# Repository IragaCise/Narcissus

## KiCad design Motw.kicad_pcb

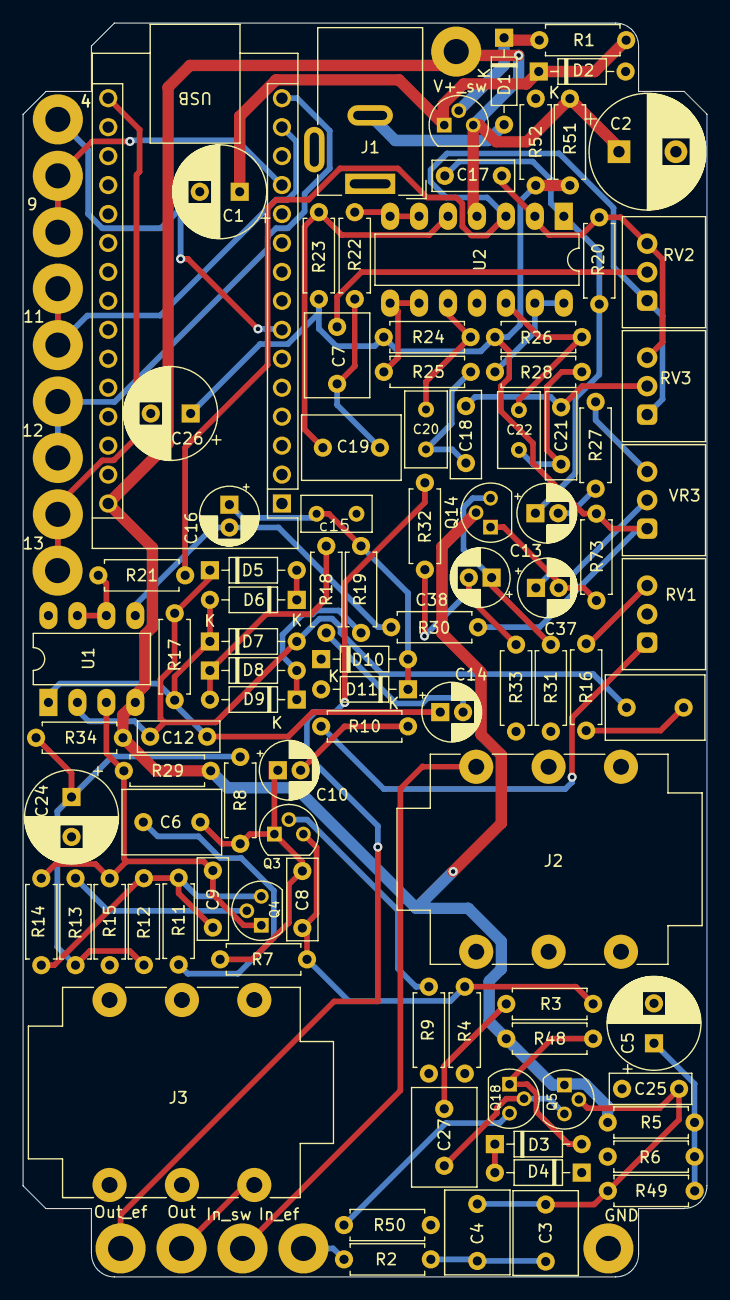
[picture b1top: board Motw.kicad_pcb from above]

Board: 2 copper layers, 60.0 x 110.0 mm, 110 parts (0 on the bottom side), 62 nets.

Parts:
4, 9, 9#2, 11, 11#2, 12, 12#2, 13, 13#2: MountingHole_Pad; MountingHole_2.2mm_M2_Pad
A1: Arduino_Nano_v3.x; Arduino_Nano
C1, C5, C26: 47u; CP_Radial_D8.0mm_P3.50mm
C2: 100u; CP_Radial_D10.0mm_P5.00mm
C3, C4: 1u; C_Rect_L7.2mm_W5.5mm_P5.00mm_FKS2_FKP2_MKS2_MKP2
C6: 47n; C_Rect_L8.5mm_W5.5mm_P5.00mm_FKS2_FKP2_MKS2_MKP2
C7: 47u; C_Rect_L7.2mm_W5.5mm_P5.00mm_FKS2_FKP2_MKS2_MKP2
C8: 100p; C_Rect_L7.0mm_W2.5mm_P5.00mm
C9: 10u; C_Rect_L7.0mm_W2.5mm_P5.00mm
C10: 47n; CP_Radial_D5.0mm_P2.00mm
C11: 100p; C_Rect_L8.5mm_W5.5mm_P5.00mm_FKS2_FKP2_MKS2_MKP2
C12: 47n; C_Rect_L7.0mm_W2.5mm_P5.00mm
C13: 100p; CP_Radial_D5.0mm_P2.00mm
C14: 1u; CP_Radial_D5.0mm_P2.00mm
C15: 68n; C_Rect_L6.0mm_W3.0mm_P3.50mm_MKS02_FKP02
C16: 4.7n; CP_Radial_D5.0mm_P2.00mm
C17: 6.8n; C_Rect_L7.0mm_W2.5mm_P5.00mm
C18: 1n; C_Rect_L7.5mm_W3.0mm_P5.00mm
C19: 1u; C_Rect_L8.5mm_W5.5mm_P5.00mm_FKS2_FKP2_MKS2_MKP2
C20: 1.5u; C_Rect_L6.5mm_W3.5mm_P3.50mm_MKS02_FKP02
C21: 0.1u; C_Rect_L7.5mm_W3.0mm_P5.00mm
C22: 0.15u; C_Rect_L6.5mm_W3.5mm_P3.50mm_MKS02_FKP02
C24: 10u; CP_Radial_D8.0mm_P3.50mm
C25: 150p; C_Rect_L7.0mm_W2.5mm_P5.00mm
C27: 10u; C_Rect_L8.5mm_W5.5mm_P5.00mm_FKS2_FKP2_MKS2_MKP2
C37, C38: 10u; CP_Radial_D5.0mm_P2.00mm
D1: 1N4007; D_DO-35_SOD27_P7.62mm_Horizontal
D2: VF=11V; D_DO-35_SOD27_P7.62mm_Horizontal
D3, D4, D5, D6, D7, D10, D11: 1N4148; D_DO-35_SOD27_P7.62mm_Horizontal
D8, D9: 1N34A; D_DO-35_SOD27_P7.62mm_Horizontal
GND: MountingHole_Pad; MountingHole_2.2mm_M2_Pad
In_ef: MountingHole_Pad; MountingHole_2.2mm_M2_Pad
In_sw: MountingHole_Pad; MountingHole_2.2mm_M2_Pad
J1: Barrel_Jack_Switch; BarrelJack_Effector
J2: AudioJack3; Jack_6.35mm_Neutrik_NMJ6HCD2_Horizontal
J3: AudioJack2; Jack_6.35mm_Neutrik_NMJ6HCD2_Horizontal
Out: MountingHole_Pad; MountingHole_2.2mm_M2_Pad
Out_ef: MountingHole_Pad; MountingHole_2.2mm_M2_Pad
Q1, Q4, Q14, Q18: 2SC2240; TO-92_231
Q3: 2SA970; TO-92_231
Q5: 2SK30A; TO-92
R1: 2.2k; R_Axial_DIN0207_L6.3mm_D2.5mm_P7.62mm_Horizontal
R2, R9, R16, R20, R24, R33: 10k; R_Axial_DIN0207_L6.3mm_D2.5mm_P7.62mm_Horizontal
R3: 1k; R_Axial_DIN0207_L6.3mm_D2.5mm_P7.62mm_Horizontal
R4, R12: 22k; R_Axial_DIN0207_L6.3mm_D2.5mm_P7.62mm_Horizontal
R5, R6, R48, R51, R52: 33k; R_Axial_DIN0207_L6.3mm_D2.5mm_P7.62mm_Horizontal
R7, R13, R21, R22, R32, R34, R73: 100k; R_Axial_DIN0207_L6.3mm_D2.5mm_P7.62mm_Horizontal
R8, R14: 470k; R_Axial_DIN0207_L6.3mm_D2.5mm_P7.62mm_Horizontal
R10: 22; R_Axial_DIN0207_L6.3mm_D2.5mm_P7.62mm_Horizontal
R11: 150; R_Axial_DIN0207_L6.3mm_D2.5mm_P7.62mm_Horizontal
R15: 120; R_Axial_DIN0207_L6.3mm_D2.5mm_P7.62mm_Horizontal
R17, R28: 68k; R_Axial_DIN0207_L6.3mm_D2.5mm_P7.62mm_Horizontal
R18: 47k; R_Axial_DIN0207_L6.3mm_D2.5mm_P7.62mm_Horizontal
R19: 220k; R_Axial_DIN0207_L6.3mm_D2.5mm_P7.62mm_Horizontal
R23: 82k; R_Axial_DIN0207_L6.3mm_D2.5mm_P7.62mm_Horizontal
R25, R26, R27: 330; R_Axial_DIN0207_L6.3mm_D2.5mm_P7.62mm_Horizontal
R29, R30: 3.3k; R_Axial_DIN0207_L6.3mm_D2.5mm_P7.62mm_Horizontal
R31: 4.7k; R_Axial_DIN0207_L6.3mm_D2.5mm_P7.62mm_Horizontal
R49: 1M; R_Axial_DIN0207_L6.3mm_D2.5mm_P7.62mm_Horizontal
R50: 470; R_Axial_DIN0207_L6.3mm_D2.5mm_P7.62mm_Horizontal
RV1: 250k; Potentiometer_RD9
RV2, RV3: 10k; Potentiometer_RD9
U1: TL072; DIP-8_W7.62mm_LongPads
U2: TL074; DIP-14_W7.62mm_LongPads
V+_sw: MountingHole_Pad; MountingHole_2.2mm_M2_Pad
VR3: 10k; Potentiometer_RD9

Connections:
+4V: C26.1, R21.1, R22.1, R23.1, R28.2, R32.2, R51.2, R52.1, R73.2, VR3.1
+8V: A1.30 (VIN), C2.1, Q1.2 (E), Q4.3 (C), Q5.1 (D), Q14.3 (C), R3.1, R5.1, R17.2, R48.2, R51.1, U1.4 (V-), U2.4 (V+), V+_sw.1
+9V: D1.1 (K), Q1.3 (C), R1.1
GND: A1.4 (GND), A1.29 (GND), C1.2, C2.2, C5.2, C7.2, C18.2, C25.2, C26.2, D2.2 (A), D4.1 (K), D10.1 (K), D11.2 (A), GND.1, J1.1, J2.S, J3.S, R6.2, R7.1, R10.1, R16.1, R33.2, R34.2, R50.2, R52.2, RV1.2, U1.8 (V+), U2.11 (V-)
unnamed: 4.1, A1.7 (D4)
unnamed: 9.1, 9#2.1, A1.12 (D9)
unnamed: 11.1, 11#2.1, A1.14 (D11)
unnamed: 12.1, 12#2.1, A1.15 (D12)
unnamed: 13.1, 13#2.1, A1.16 (D13)
unnamed: C3.2, C4.2, R2.2
unnamed: C5.1, R5.2, R6.1, R49.2
unnamed: C6.2, R4.1
unnamed: C7.1, R3.2, R9.2, R13.2, R15.2
unnamed: C9.2, R11.2
unnamed: C10.2, R12.1
unnamed: C12.2, R18.2
unnamed: C14.2, R20.1
unnamed: C15.2, C20.1, R25.2
unnamed: C16.2, C21.1, R26.2
unnamed: C17.2, C22.1, R27.2
unnamed: C20.2, RV2.2
unnamed: C21.2, C22.2, RV3.2
unnamed: C24.1, R30.2, U2.1
unnamed: C24.2, R31.2
unnamed: C37.1, VR3.2
unnamed: D1.2 (A), J1.2
unnamed: C1.1, D2.1 (K), Q1.1 (B), R1.2
unnamed: D3.2 (A), Q18.1 (B), R48.1
unnamed: D3.1 (K), D4.2 (A)
unnamed: D5.2 (A), D7.1 (K)
unnamed: C12.1, C13.1, D5.1 (K), D6.2 (A), R19.1, U1.2 (-)
unnamed: C13.2, C14.1, D6.1 (K), D7.2 (A), R19.2, U1.1
unnamed: D8.2 (A), D9.1 (K), R24.1
unnamed: D8.1 (K), D9.2 (A), R20.2
unnamed: C18.1, C19.1, D10.2 (A), D11.1 (K), R24.2
unnamed: In_ef.1, R2.1
unnamed: In_sw.1, J2.T
unnamed: J3.T, Out_ef.1
unnamed: C8.1, R4.2, R7.2, R8.1
unnamed: C8.2, C9.1, C10.1, R8.2, R9.1
unnamed: C11.1, Q3.2 (B), R12.2, R13.1, R14.1
unnamed: C11.2, Q3.1 (C), R14.2, R16.2, R17.1, U1.3 (+)
unnamed: Q3.3 (E), R15.1
unnamed: C27.2, Q4.1 (B), R32.1
unnamed: Q4.2 (E), R33.1
unnamed: C3.1, C4.1, C25.1, Q5.2 (G), R49.1
unnamed: C37.2, Q14.1 (B), R73.1
unnamed: C38.1, Q14.2 (E)
unnamed: C6.1, Q5.3 (S), Q18.3 (C)
unnamed: Q18.2 (E), R50.1
unnamed: R11.1, RV1.1
unnamed: R18.1, RV1.3
unnamed: C19.2, R28.1, U1.5 (+)
unnamed: R29.1, U1.6 (-), U1.7
unnamed: R29.2, RV2.1, RV3.1, U2.3 (+)
unnamed: R30.1, RV2.3, RV3.3, U2.2 (-)
unnamed: C15.1, R21.2, U2.5 (+)
unnamed: R25.1, U2.6 (-), U2.7
unnamed: C16.1, R22.2, U2.10 (+)
unnamed: R26.1, U2.8, U2.9 (-)
unnamed: C17.1, R23.2, U2.12 (+)
unnamed: R27.1, U2.13 (-), U2.14

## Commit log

2026-01-06 v2.0.1
